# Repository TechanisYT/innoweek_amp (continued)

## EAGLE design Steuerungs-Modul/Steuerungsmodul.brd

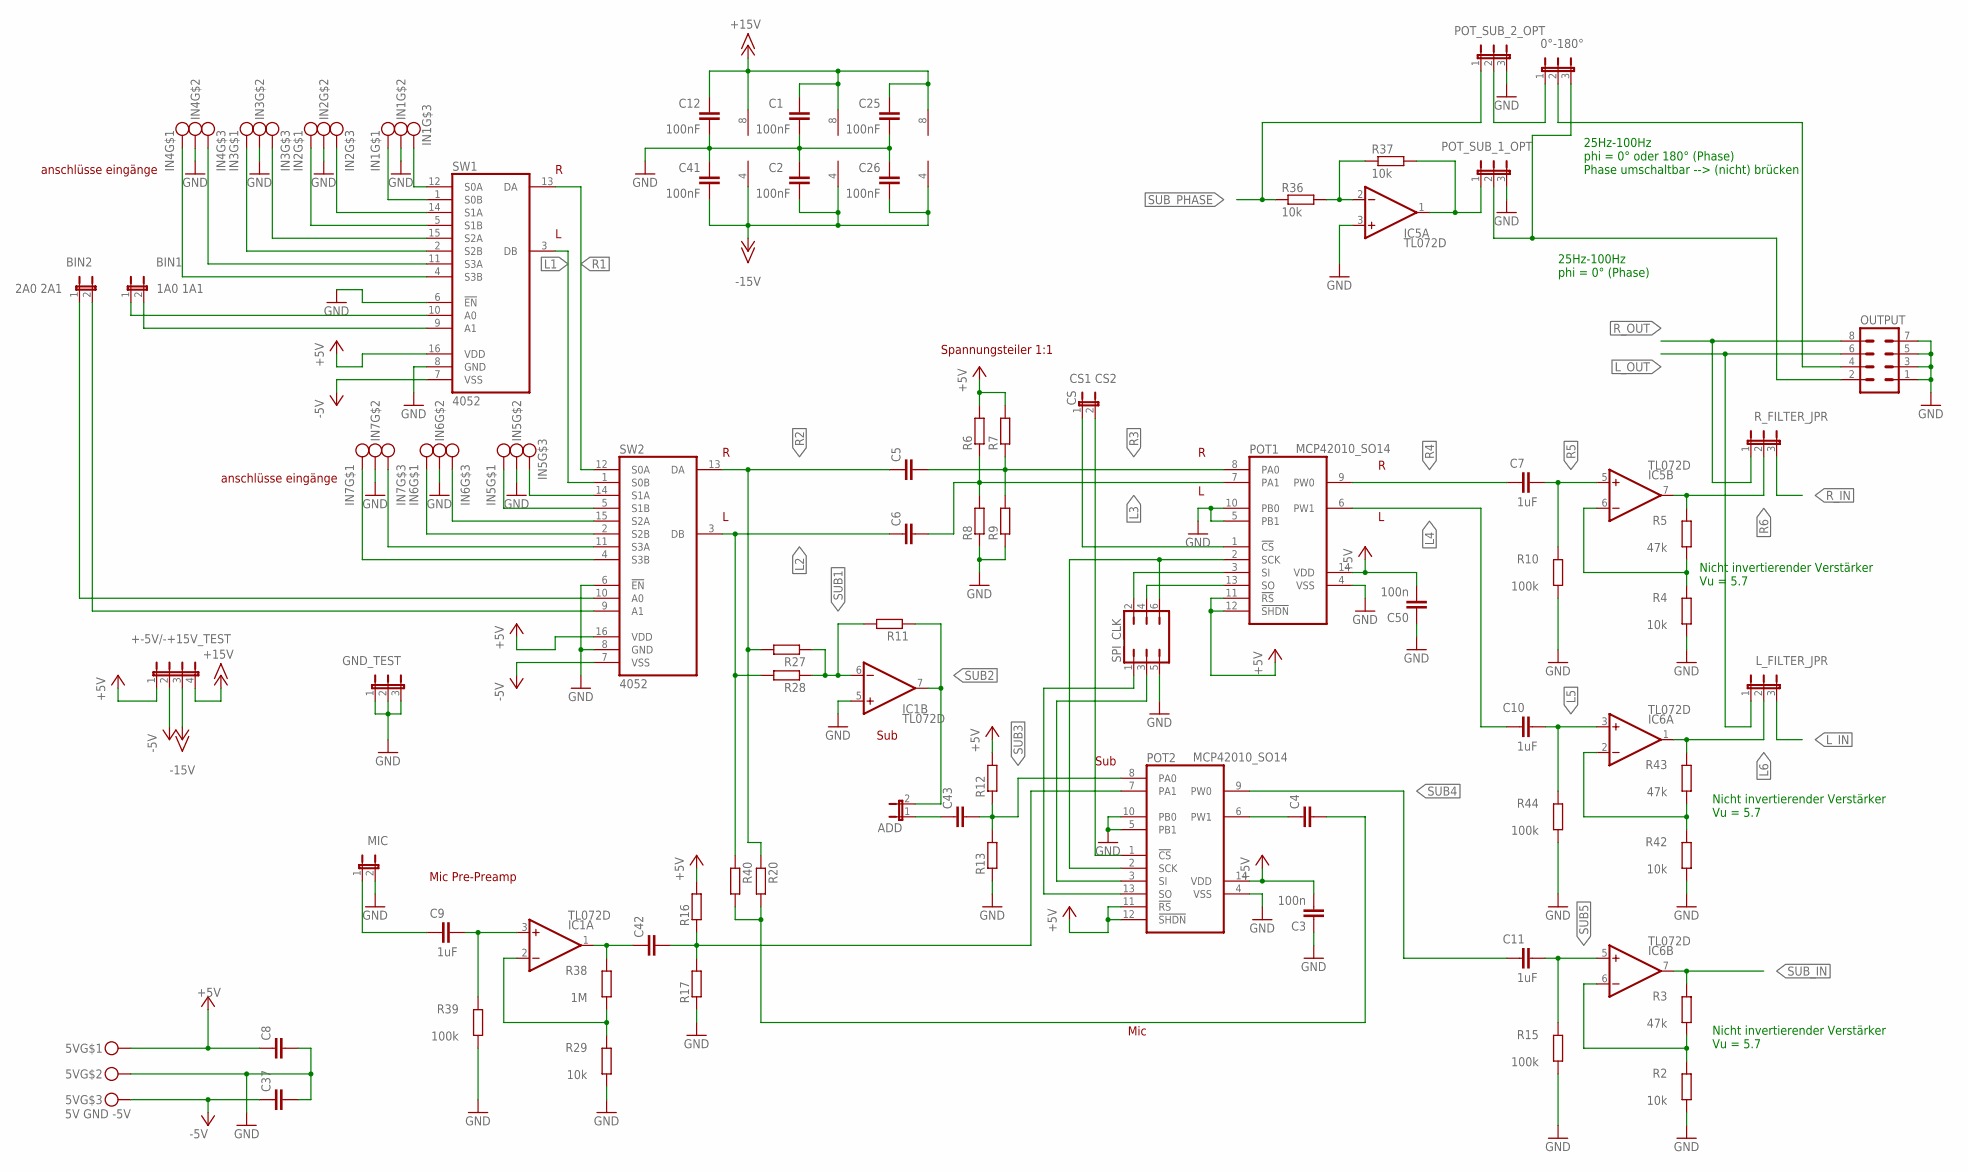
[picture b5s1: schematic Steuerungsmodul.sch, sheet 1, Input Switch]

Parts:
0°-180°: JMP3
5V: 5V GND -5V; MKDS3/3_5,08
+-5V/-+15V_TEST: JP4E; JP4
ADD: JMP2
BIN1: 1A0 1A1; JMP2
BIN2: 2A0 2A1; JMP2
C1, C2, C12, C25, C26, C41: 100nF; C0805
C3, C50: 100n; C0805
C4, C5, C6, C8, C37, C42, C43: C-EUC0805; C0805
C7, C9, C10, C11: 1uF; C025-025X050
CS: CS1 CS2; JMP2
FRAME1: HTL-A3-H; HTL-LEER
GND_TEST: JMP3
IC1, IC5, IC6: TL072D; SO08
IN1, IN2, IN3, IN4, IN5, IN6, IN7: MKDS3/3_5,08
L_FILTER_JPR: JMP3
MIC: JMP2
OUTPUT: MA04-2
POT1, POT2: MCP42010_SO14; SO14
POT_SUB_1_OPT, POT_SUB_2_OPT: JMP3
R2, R4, R29, R36, R37, R42: 10k; M0805
R3, R5, R43: 47k; M0805
R6, R7, R8, R9, R11, R12, R13, R16, R17, R20, R27, R28, R40: R-EU_M0805; M0805
R10, R15, R39, R44: 100k; M0805
R38: 1M; M0805
R_FILTER_JPR: JMP3
SPI_CLK: JP3Q
SW1, SW2: 4052; SO-16

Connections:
1A0: BIN1.1, SW1.10 (A0)
1A1: BIN1.2, SW1.9 (A1)
2A0: BIN2.1, SW2.10 (A0)
2A1: BIN2.2, SW2.9 (A1)
+5V: 5V.P$1, +-5V/-+15V_TEST.1, C3.2, C8.1, C50.2, POT1.11 (!RS), POT1.12 (!SHDN), POT1.14 (VDD), POT2.11 (!RS), POT2.12 (!SHDN), POT2.14 (VDD), R6.2, R7.2, R12.2, R16.2, SW1.16 (VDD), SW2.16 (VDD)
+15V: +-5V/-+15V_TEST.4, C1.1, C12.1, C25.1, IC1.8 (V+), IC5.8 (V+), IC6.8 (V+); also elsewhere on the board
-5V: 5V.P$3, +-5V/-+15V_TEST.2, C37.1, SW1.7 (VSS), SW2.7 (VSS)
-15V: +-5V/-+15V_TEST.3, C2.2, C26.2, C41.2, IC1.4 (V-), IC5.4 (V-), IC6.4 (V-); also elsewhere on the board
GND: 5V.P$2, C1.2, C2.1, C3.1, C8.2, C12.2, C25.2, C26.1, C37.2, C41.1, C50.1, GND_TEST.1, GND_TEST.2, GND_TEST.3, IC1.5 (+IN), IC5.3 (+IN), IN1.P$2, IN2.P$2, IN3.P$2, IN4.P$2, IN5.P$2, IN6.P$2, IN7.P$2, MIC.2, OUTPUT.1, OUTPUT.3, OUTPUT.5, OUTPUT.7, POT1.4 (VSS), POT1.5 (PB1), POT1.10 (PB0), POT2.4 (VSS), POT2.5 (PB1), POT2.10 (PB0), POT_SUB_1_OPT.3, POT_SUB_2_OPT.3, R2.1, R4.1, R8.1, R9.1, R10.1, R13.1, R15.1, R17.1, R29.1, R39.1, R42.1, R44.1, SPI_CLK.5, SW1.6 (!EN), SW1.8 (GND), SW2.6 (!EN), SW2.8 (GND); also elsewhere on the board
L1: SW1.3 (DB), SW2.1 (S0B)
L2: C6.1, R28.2, R40.1, SW2.3 (DB)
L3: C6.2, POT1.7 (PA1), R6.1, R8.2
L4: C10.1, POT1.6 (PW1)
L5: C10.2, IC6.3 (+IN), R44.2
L6: IC6.1 (OUT), L_FILTER_JPR.2, R43.2
L_IN: L_FILTER_JPR.3; also elsewhere on the board
L_OUT: L_FILTER_JPR.1, OUTPUT.6; also elsewhere on the board
unnamed: CS.2, POT2.1 (!CS)
unnamed: CS.1, POT1.1 (!CS)
unnamed: IC5.1 (OUT), POT_SUB_1_OPT.1, R37.2
unnamed: POT1.3 (SI), SPI_CLK.2
unnamed: IC6.2 (-IN), R42.2, R43.1
unnamed: IC6.6 (-IN), R2.2, R3.1
unnamed: POT2.13 (SO), SPI_CLK.1
unnamed: IC5.6 (-IN), R4.2, R5.1
unnamed: C9.1, MIC.1
unnamed: POT1.13 (SO), SPI_CLK.4
unnamed: POT2.3 (SI), SPI_CLK.3
unnamed: C4.1, POT2.6 (PW1)
unnamed: C42.2, POT2.7 (PA1), R16.1, R17.2
unnamed: POT1.2 (SCK), POT2.2 (SCK), SPI_CLK.6
unnamed: IN1.P$3, SW1.12 (S0A)
unnamed: IN1.P$1, SW1.1 (S0B)
unnamed: IN2.P$3, SW1.14 (S1A)
unnamed: IN2.P$1, SW1.5 (S1B)
unnamed: IN3.P$3, SW1.15 (S2A)
unnamed: IN3.P$1, SW1.2 (S2B)
unnamed: IN4.P$3, SW1.11 (S3A)
unnamed: IN4.P$1, SW1.4 (S3B)
unnamed: IN5.P$3, SW2.14 (S1A)
unnamed: IN5.P$1, SW2.5 (S1B)
unnamed: IN6.P$3, SW2.15 (S2A)
unnamed: IN6.P$1, SW2.2 (S2B)
unnamed: IN7.P$3, SW2.11 (S3A)
unnamed: IN7.P$1, SW2.4 (S3B)
unnamed: C9.2, IC1.3 (+IN), R39.2
unnamed: IC1.2 (-IN), R29.2, R38.1
unnamed: ADD.1, C43.1
unnamed: C42.1, IC1.1 (OUT), R38.2
unnamed: C4.2, R20.2, R40.2
unnamed: IC5.2 (-IN), R36.2, R37.1
unnamed: 0°-180°.1, POT_SUB_2_OPT.2
R1: SW1.13 (DA), SW2.12 (S0A)
R2: C5.1, R20.1, R27.2, SW2.13 (DA)
R3: C5.2, POT1.8 (PA0), R7.1, R9.2
R4: C7.1, POT1.9 (PW0)
R5: C7.2, IC5.5 (+IN), R10.2
R6: IC5.7 (OUT), R5.2, R_FILTER_JPR.2
R_IN: R_FILTER_JPR.3; also elsewhere on the board
R_OUT: OUTPUT.8, R_FILTER_JPR.1; also elsewhere on the board
SUB1: IC1.6 (-IN), R11.2, R27.1, R28.1
SUB2: ADD.2, IC1.7 (OUT), R11.1
SUB3: C43.2, POT2.8 (PA0), R12.1, R13.2
SUB4: C11.1, POT2.9 (PW0)
SUB5: C11.2, IC6.5 (+IN), R15.2
SUB_IN: IC6.7 (OUT), R3.2; also elsewhere on the board
SUB_OUT_1: 0°-180°.3, OUTPUT.2, POT_SUB_1_OPT.2
SUB_OUT_2: 0°-180°.2, OUTPUT.4
SUB_PHASE: POT_SUB_2_OPT.1, R36.1; also elsewhere on the board

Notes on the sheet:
Spannungsteiler 1:1
Sub
anschlüsse eingänge
Mic Pre-Preamp
Mic
Nicht invertierender Verstärker Vu = 5.7
25Hz-100Hz phi = 0° oder 180° (Phase) Phase umschaltbar --> (nicht) brücken
25Hz-100Hz phi = 0° (Phase)

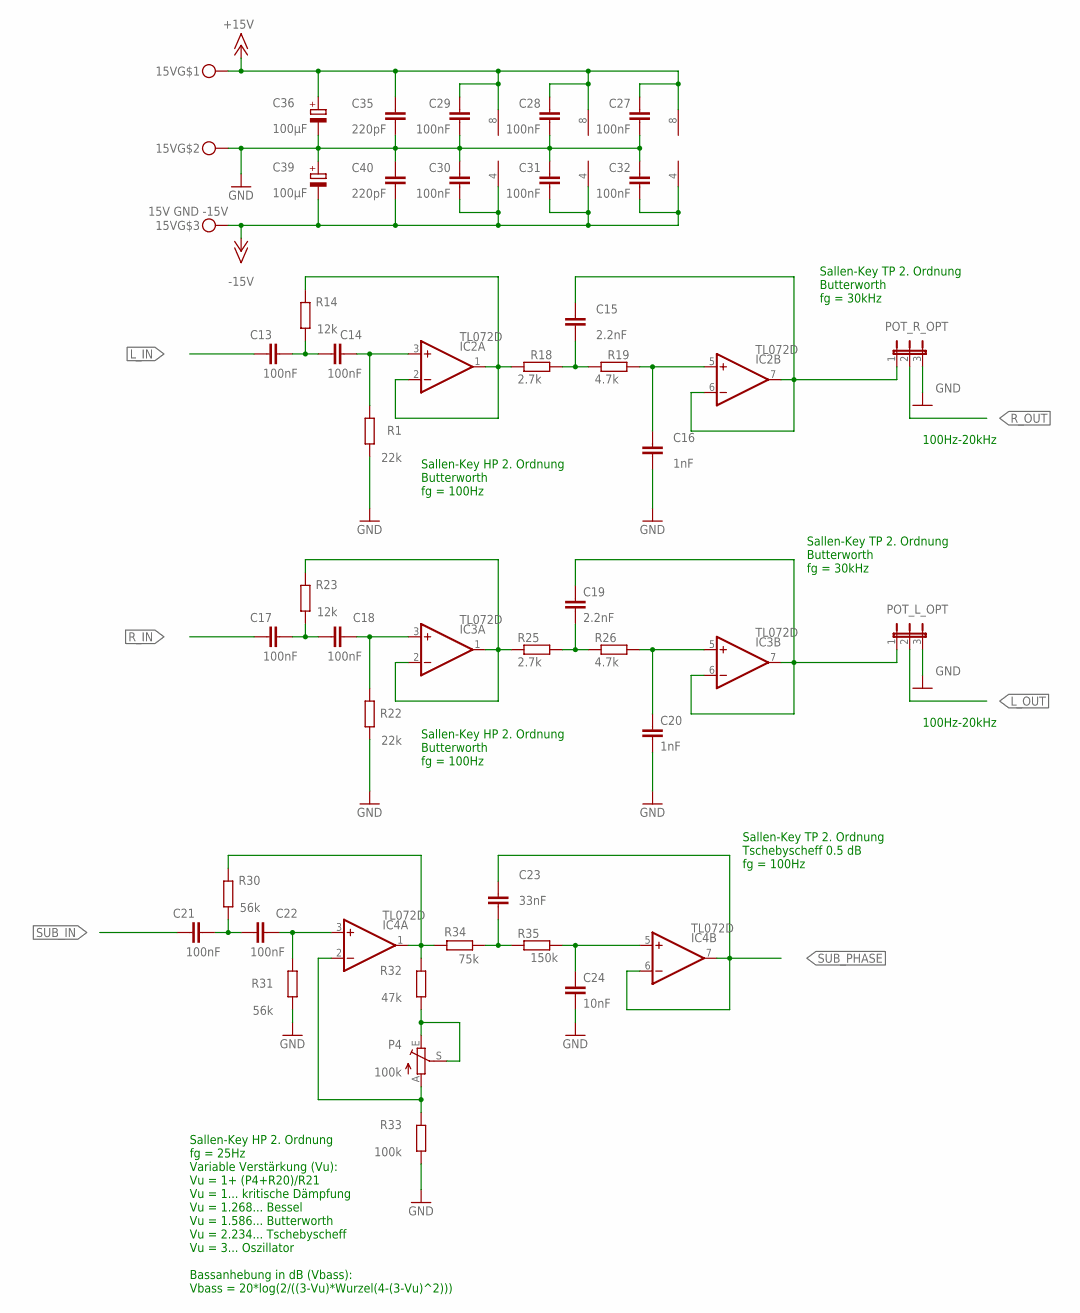
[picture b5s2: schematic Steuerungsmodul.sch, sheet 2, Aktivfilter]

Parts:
15V: 15V GND -15V; MKDS3/3_5,08
C13, C14, C17, C18, C21, C22, C27, C28, C29, C30, C31, C32: 100nF; C0805
C15, C19: 2.2nF; C0805
C16, C20: 1nF; C0805
C23: 33nF; C0805
C24: 10nF; C0805
C35, C40: 220pF; C0805
C36, C39: 100µF; E2,5-6
FRAME2: HTL-A3-H; HTL-LEER
IC2, IC3, IC4: TL072D; SO08
P4: 100k; S64W
POT_L_OPT: JMP3
POT_R_OPT: JMP3
R1, R22: 22k; M0805
R14, R23: 12k; M0805
R18, R25: 2.7k; M0805
R19, R26: 4.7k; M0805
R30, R31: 56k; M0805
R32: 47k; M0805
R33: 100k; M0805
R34: 75k; M0805
R35: 150k; M0805

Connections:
+15V: 15V.P$1, C27.1, C28.1, C29.1, C35.1, C36.+, IC2.8 (V+), IC3.8 (V+), IC4.8 (V+); also elsewhere on the board
-15V: 15V.P$3, C30.2, C31.2, C32.2, C39.-, C40.2, IC2.4 (V-), IC3.4 (V-), IC4.4 (V-); also elsewhere on the board
GND: 15V.P$2, C16.2, C20.2, C24.2, C27.2, C28.2, C29.2, C30.1, C31.1, C32.1, C35.2, C36.-, C39.+, C40.1, POT_L_OPT.3, POT_R_OPT.3, R1.1, R22.1, R31.1, R33.1; also elsewhere on the board
L_IN: C13.1; also elsewhere on the board
L_OUT: POT_L_OPT.2; also elsewhere on the board
unnamed: IC2.1 (OUT), IC2.2 (-IN), R14.2, R18.1
unnamed: C14.2, IC2.3 (+IN), R1.2
unnamed: C13.2, C14.1, R14.1
unnamed: C15.2, R18.2, R19.1
unnamed: C16.1, IC2.5 (+IN), R19.2
unnamed: C15.1, IC2.6 (-IN), IC2.7 (OUT), POT_R_OPT.1
unnamed: IC3.1 (OUT), IC3.2 (-IN), R23.2, R25.1
unnamed: C18.2, IC3.3 (+IN), R22.2
unnamed: C17.2, C18.1, R23.1
unnamed: C19.2, R25.2, R26.1
unnamed: C20.1, IC3.5 (+IN), R26.2
unnamed: C19.1, IC3.6 (-IN), IC3.7 (OUT), POT_L_OPT.1
unnamed: C21.2, C22.1, R30.1
unnamed: C22.2, IC4.3 (+IN), R31.2
unnamed: IC4.1 (OUT), R30.2, R32.2, R34.2
unnamed: IC4.2 (-IN), P4.A, R33.2
unnamed: P4.E, P4.S, R32.1
unnamed: C24.1, IC4.5 (+IN), R35.2
unnamed: C23.2, R34.1, R35.1
R_IN: C17.1; also elsewhere on the board
R_OUT: POT_R_OPT.2; also elsewhere on the board
SUB_IN: C21.1; also elsewhere on the board
SUB_PHASE: C23.1, IC4.6 (-IN), IC4.7 (OUT); also elsewhere on the board

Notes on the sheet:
100Hz-20kHz
Sallen-Key TP 2. Ordnung Butterworth fg = 30kHz
Sallen-Key HP 2. Ordnung Butterworth fg = 100Hz
Sallen-Key TP 2. Ordnung Tschebyscheff 0.5 dB fg = 100Hz
Sallen-Key HP 2. Ordnung fg = 25Hz Variable Verstärkung (Vu): Vu = 1+ (P4+R20)/R21 Vu = 1... kritische Dämpfung Vu = 1.268... Bessel Vu = 1.586... Butterworth Vu = 2.234... Tschebyscheff Vu = 3... Oszillator Bassanhebung in dB (Vbass): Vbass = 20*log(2/((3-Vu)*Wurzel(4-(3-Vu)^2)))

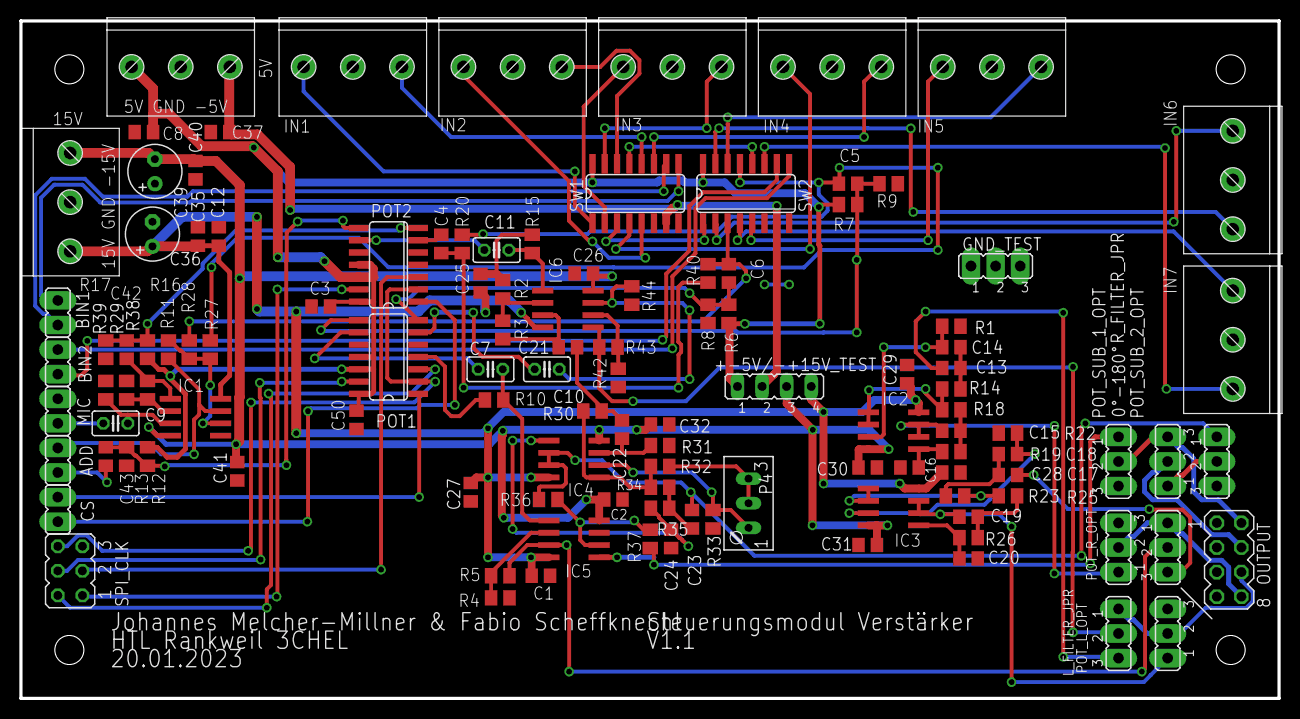
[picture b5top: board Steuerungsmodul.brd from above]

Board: 2 copper layers, 130.0 x 70.0 mm, 121 parts (0 on the bottom side), 88 nets.

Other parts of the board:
U$1: HTL-A4-H

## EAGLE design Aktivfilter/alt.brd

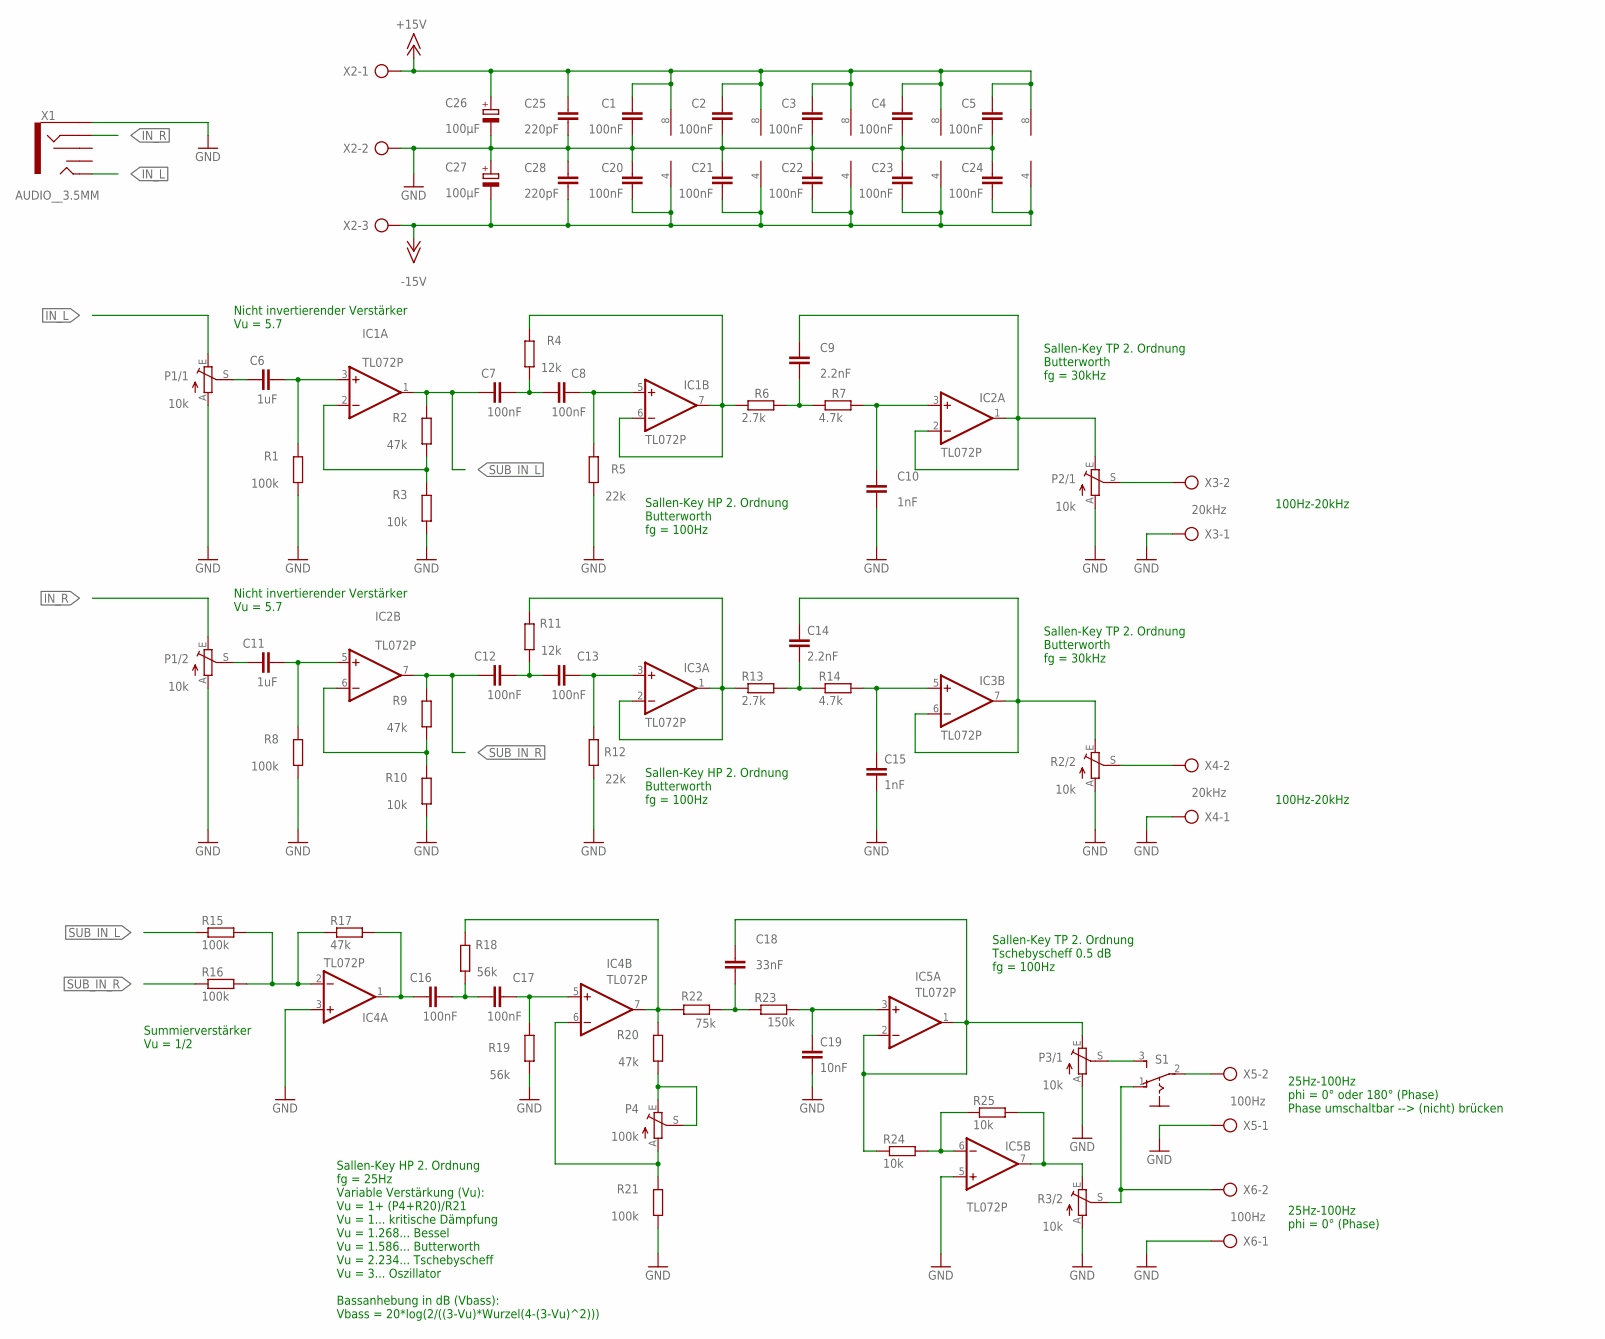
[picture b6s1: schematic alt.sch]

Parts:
C1, C2, C3, C4, C5, C7, C8, C12, C13, C17, C20, C21, C22, C23, C24: 100nF; C025-025X050
C6, C11: 1uF; C025-025X050
C9, C14: 2.2nF; C025-025X050
C10, C15: 1nF; C025-025X050
C16: 100nF; C050-025X075
C18: 33nF; C025-025X050
C19: 10nF; C025-025X050
C25, C28: 220pF; C025-025X050
C26, C27: 100µF; E2,5-6
IC1, IC2, IC3, IC4, IC5: TL072P; DIL08
P1/1, P1/2, P2/1, P3/1: 10k; B64Y
P4: 100k; B64Y
R1, R15, R16, R21: 100k; 0207/10
R2, R17, R20: 47k; 0207/10
R2/2, R3/2: 10k; B64Y
R3, R10, R24, R25: 10k; 0207/10
R4, R11: 12k; 0207/10
R5, R12: 22k; 0207/10
R6, R13: 2.7k; 0207/10
R7, R14: 4.7k; 0207/10
R8: 100k; 0207/7
R9: 47k; 0207/7
R18: 56k; 0207/10
R19: 56k; 0207/7
R22: 75k; 0207/7
R23: 150k; 0207/10
S1: 255SB
X1: AUDIO__3.5MM; AUDIO-JACK
X2: AK300/3
X3, X4: 20kHz; AK300/2
X5, X6: 100Hz; AK300/2

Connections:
+15V: C1.1, C2.1, C3.1, C4.1, C5.1, C25.1, C26.+, IC1.8 (V+), IC2.8 (V+), IC3.8 (V+), IC4.8 (V+), IC5.8 (V+), X2.1
-15V: C20.2, C21.2, C22.2, C23.2, C24.2, C27.-, C28.2, IC1.4 (V-), IC2.4 (V-), IC3.4 (V-), IC4.4 (V-), IC5.4 (V-), X2.3
GND: C1.2, C2.2, C3.2, C4.2, C5.2, C10.2, C15.2, C19.2, C20.1, C21.1, C22.1, C23.1, C24.1, C25.2, C26.-, C27.+, C28.1, IC4.3 (+IN), IC5.5 (+IN), P1/1.A, P1/2.A, P2/1.A, P3/1.A, R1.1, R2/2.A, R3.1, R3/2.A, R5.1, R8.1, R10.1, R12.1, R19.1, R21.1, X1.SLEEVE, X2.2, X3.1, X4.1, X5.1, X6.1
IN_L: P1/1.E, X1.TIP
IN_R: P1/2.E, X1.RING
unnamed: P3/1.S, S1.3 (S)
unnamed: R3/2.S, S1.1 (O), X6.2
unnamed: S1.2, X5.2
unnamed: C6.1, P1/1.S
unnamed: C6.2, IC1.3 (+IN), R1.2
unnamed: IC1.2 (-IN), R2.1, R3.2
unnamed: IC1.6 (-IN), IC1.7 (OUT), R4.2, R6.1
unnamed: C8.2, IC1.5 (+IN), R5.2
unnamed: C7.2, C8.1, R4.1
unnamed: IC4.2 (-IN), R15.2, R16.2, R17.1
unnamed: C9.2, R6.2, R7.1
unnamed: C10.1, IC2.3 (+IN), R7.2
unnamed: C9.1, IC2.1 (OUT), IC2.2 (-IN), P2/1.E
unnamed: C16.1, IC4.1 (OUT), R17.2
unnamed: C11.1, P1/2.S
unnamed: C11.2, IC2.5 (+IN), R8.2
unnamed: IC2.6 (-IN), R9.1, R10.2
unnamed: IC3.1 (OUT), IC3.2 (-IN), R11.2, R13.1
unnamed: C13.2, IC3.3 (+IN), R12.2
unnamed: C12.2, C13.1, R11.1
unnamed: C14.2, R13.2, R14.1
unnamed: C15.1, IC3.5 (+IN), R14.2
unnamed: C14.1, IC3.6 (-IN), IC3.7 (OUT), R2/2.E
unnamed: C16.2, C17.1, R18.1
unnamed: C17.2, IC4.5 (+IN), R19.2
unnamed: IC4.7 (OUT), R18.2, R20.2, R22.2
unnamed: IC4.6 (-IN), P4.A, R21.2
unnamed: IC5.6 (-IN), R24.2, R25.1
unnamed: P4.E, P4.S, R20.1
unnamed: C19.1, IC5.3 (+IN), R23.2
unnamed: C18.2, R22.1, R23.1
OUT_L: P2/1.S, X3.2
OUT_R: R2/2.S, X4.2
SUB_IN_L: C7.1, IC1.1 (OUT), R2.2, R15.1
SUB_IN_R: C12.1, IC2.7 (OUT), R9.2, R16.1
SUB_OUT: IC5.7 (OUT), R3/2.E, R25.2
SUB_OUT-180: C18.1, IC5.1 (OUT), IC5.2 (-IN), P3/1.E, R24.1

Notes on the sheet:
100Hz-20kHz
25Hz-100Hz phi = 0° oder 180° (Phase) Phase umschaltbar --> (nicht) brücken
25Hz-100Hz phi = 0° (Phase)
Sallen-Key TP 2. Ordnung Butterworth fg = 30kHz
Sallen-Key HP 2. Ordnung Butterworth fg = 100Hz
Nicht invertierender Verstärker Vu = 5.7
Summierverstärker Vu = 1/2
Sallen-Key TP 2. Ordnung Tschebyscheff 0.5 dB fg = 100Hz
Sallen-Key HP 2. Ordnung fg = 25Hz Variable Verstärkung (Vu): Vu = 1+ (P4+R20)/R21 Vu = 1... kritische Dämpfung Vu = 1.268... Bessel Vu = 1.586... Butterworth Vu = 2.234... Tschebyscheff Vu = 3... Oszillator Bassanhebung in dB (Vbass): Vbass = 20*log(2/((3-Vu)*Wurzel(4-(3-Vu)^2)))

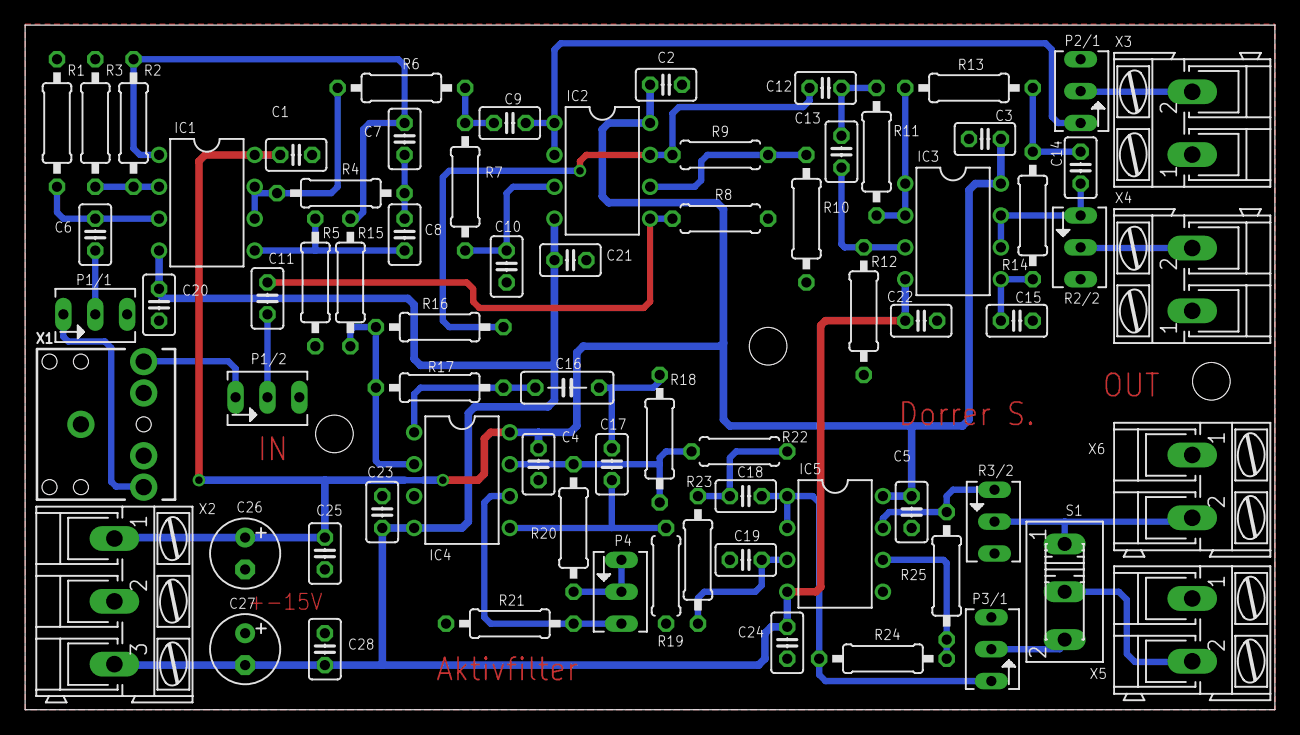
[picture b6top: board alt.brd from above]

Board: 2 copper layers, 99.5 x 54.5 mm, 72 parts (0 on the bottom side), 42 nets.

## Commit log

2023-11-27 initial
